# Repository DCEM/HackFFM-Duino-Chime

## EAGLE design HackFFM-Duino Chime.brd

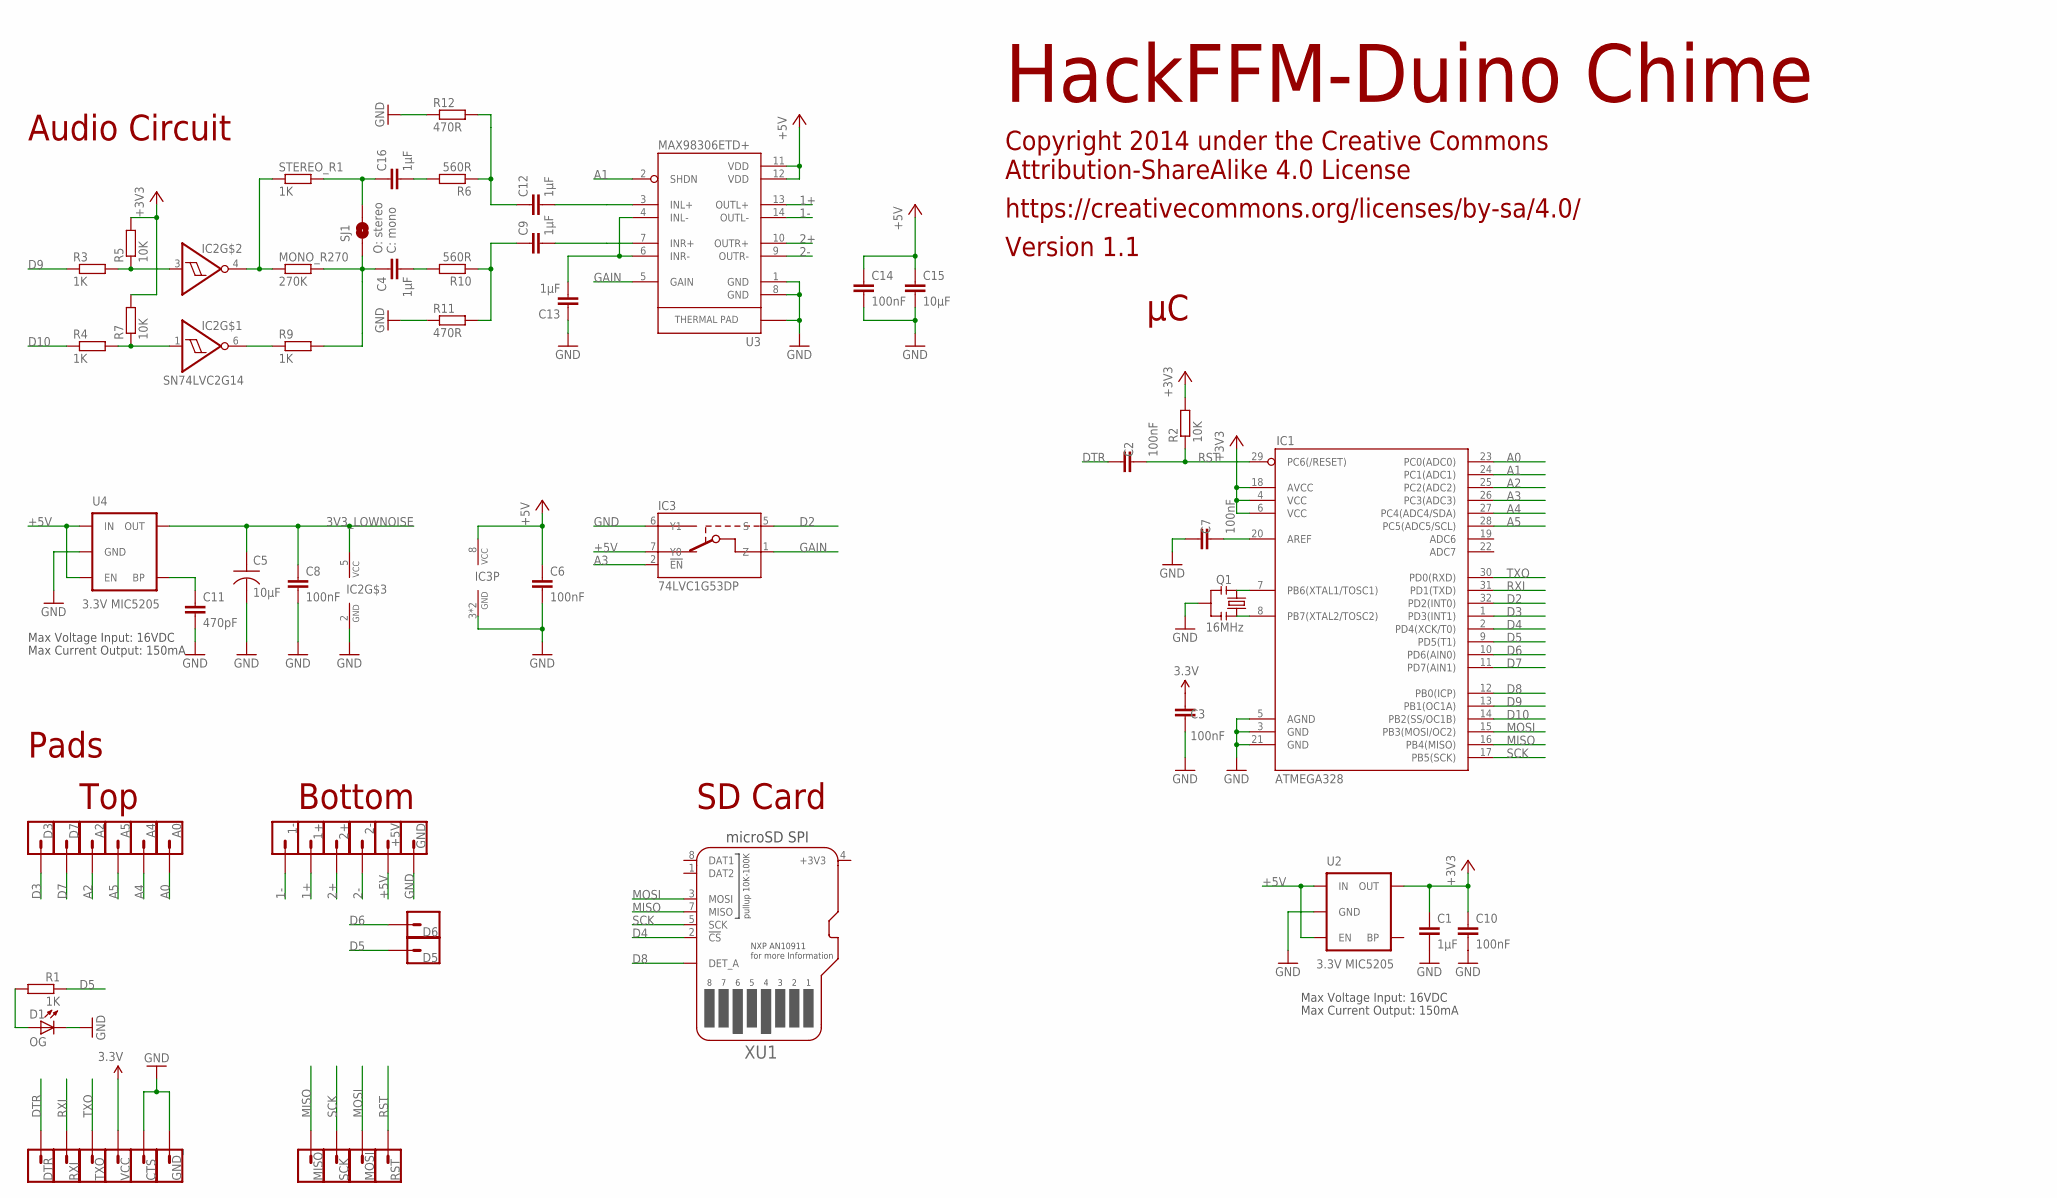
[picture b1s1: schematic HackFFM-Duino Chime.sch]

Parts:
1+, 1-, 2+, 2-: M01M01_SMD_EDGE_SHORT; M01_SMD_EDGE_SHORT
+5V: M01M01_SMD_EDGE_SHORT; M01_SMD_EDGE_SHORT
A0, A2, A4, A5: M01M01_SMD_EDGE_SHORT; M01_SMD_EDGE_SHORT
C1, C4, C9, C12, C13, C16: 1µF; C0402
C2, C3, C6, C7, C8, C10, C14: 100nF; C0402
C5: 10µF; TAN-A
C11: 470pF; C0402
C15: 10µF; C0805
CTS: M01M01_SMD_EDGE_XS; M01_SMD_EDGE_XS
D1: OG; LED-0603
D3, D5, D6, D7: M01M01_SMD_EDGE_SHORT; M01_SMD_EDGE_SHORT
DTR: M01M01_SMD_EDGE_XS; M01_SMD_EDGE_XS
GND: M01M01_SMD_EDGE_SHORT; M01_SMD_EDGE_SHORT
GND_: M01M01_SMD_EDGE_XS; M01_SMD_EDGE_XS
IC1: ATMEGA328; TQFP32-08
IC2: SN74LVC2G14; DCK_(R-PDSO-G6)
IC3: 74LVC1G53DP; SOT-505-2
MISO: M01M01_SMD_EDGE_XS; M01_SMD_EDGE_XS
MONO_R270: 270K; R0805_NOCREAM
MOSI: M01M01_SMD_EDGE_XS; M01_SMD_EDGE_XS
Q1: 16MHz; RESONATOR-SMD
R1, R3, R4, R9: 1K; R0402
R2, R5, R7: 10K; R0402
R6, R10: 560R; R0402
R11, R12: 470R; R0402
RST: M01M01_SMD_EDGE_XS; M01_SMD_EDGE_XS
RXI: M01M01_SMD_EDGE_XS; M01_SMD_EDGE_XS
SCK: M01M01_SMD_EDGE_XS; M01_SMD_EDGE_XS
SJ1: SOLDERJUMPERNO; SJ_2S-NO
STEREO_R1: 1K; R0805_NOCREAM
TXO: M01M01_SMD_EDGE_XS; M01_SMD_EDGE_XS
U2, U4: 3.3V MIC5205; SOT23-5
U3: MAX98306ETD+; 14-TDFN
VCC: M01M01_SMD_EDGE_XS; M01_SMD_EDGE_XS
XU1: MICROSD_DETMOLEX104031; MICROSD_MOLEX_104031

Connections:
1+: 1+.P$1, U3.13 (OUTL+)
1-: 1-.P$1, U3.14 (OUTL-)
2+: 2+.P$1, U3.10 (OUTR+)
2-: 2-.P$1, U3.9 (OUTR-)
3V3_LOWNOISE: C5.1, C8.1, IC2.5 (VCC), U4.5 (OUT)
+3V3: C1.1, C3.2, C10.1, IC1.4 (VCC), IC1.6 (VCC), IC1.18 (AVCC), R2.2, R5.2, R7.2, U2.5 (OUT), VCC.P$1, XU1.4 (+3V3)
+5V: +5V.P$1, C6.1, C14.1, C15.1, IC3.7 (Y0), IC3.8 (VCC), U2.1 (IN), U2.3 (EN), U3.11 (VDD), U3.12 (VDD), U4.1 (IN), U4.3 (EN)
A0: A0.P$1, IC1.23 (PC0(ADC0))
A1: IC1.24 (PC1(ADC1)), U3.2 (SHDN)
A2: A2.P$1, IC1.25 (PC2(ADC2))
A3: IC1.26 (PC3(ADC3)), IC3.2 (!EN)
A4: A4.P$1, IC1.27 (PC4(ADC4/SDA))
A5: A5.P$1, IC1.28 (PC5(ADC5/SCL))
D2: IC1.32 (PD2(INT0)), IC3.5 (S)
D3: D3.P$1, IC1.1 (PD3(INT1))
D4: IC1.2 (PD4(XCK/T0)), XU1.2 (!CS)
D5: D5.P$1, IC1.9 (PD5(T1)), R1.1
D6: D6.P$1, IC1.10 (PD6(AIN0))
D7: D7.P$1, IC1.11 (PD7(AIN1))
D8: IC1.12 (PB0(ICP)), XU1.DET_A
D9: IC1.13 (PB1(OC1A)), R3.1
D10: IC1.14 (PB2(SS/OC1B)), R4.1
DTR: C2.2, DTR.P$1
GAIN: IC3.1 (Z), U3.5 (GAIN)
GND: C1.2, C3.1, C5.2, C6.2, C7.2, C8.2, C10.2, C11.2, C13.1, C14.2, C15.2, CTS.P$1, D1.C, GND.P$1, GND_.P$1, IC1.3 (GND), IC1.5 (AGND), IC1.21 (GND), IC2.2 (GND), IC3.3 (GND), IC3.4 (GND), IC3.6 (Y1), Q1.2, R11.1, R12.1, U2.2 (GND), U3.1 (GND), U3.8 (GND), U3.15 (GND), U4.2 (GND), XU1.6 (GND), XU1.DET_B (GND), XU1.G1 (GND), XU1.G2 (GND), XU1.G3 (GND), XU1.G4 (GND)
MISO: IC1.16 (PB4(MISO)), MISO.P$1, XU1.7 (MISO)
MOSI: IC1.15 (PB3(MOSI/OC2)), MOSI.P$1, XU1.3 (MOSI)
unnamed: IC1.8 (PB7(XTAL2/TOSC2)), Q1.1
unnamed: IC1.7 (PB6(XTAL1/TOSC1)), Q1.3
unnamed: D1.A, R1.2
unnamed: C16.2, R6.2
unnamed: IC2.1 (I), R4.2, R7.1
unnamed: C11.1, U4.4 (BP)
unnamed: C12.1, R6.1, R12.2
unnamed: IC2.3 (I), R3.2, R5.1
unnamed: IC2.6 (O), R9.1
unnamed: IC2.4 (O), MONO_R270.1, STEREO_R1.1
unnamed: C4.2, R10.2
unnamed: C9.1, R10.1, R11.2
unnamed: C9.2, U3.7 (INR+)
unnamed: C4.1, MONO_R270.2, R9.2, SJ1.1
unnamed: C16.1, SJ1.2, STEREO_R1.2
unnamed: C7.1, IC1.20 (AREF)
unnamed: C13.2, U3.4 (INL-), U3.6 (INR-)
unnamed: C12.2, U3.3 (INL+)
RST: C2.1, IC1.29 (PC6(/RESET)), R2.1, RST.P$1
RXI: IC1.31 (PD1(TXD)), RXI.P$1
SCK: IC1.17 (PB5(SCK)), SCK.P$1, XU1.5 (SCK)
TXO: IC1.30 (PD0(RXD)), TXO.P$1

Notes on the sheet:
Max Voltage Input: 16VDC
Max Current Output: 150mA
HackFFM-Duino Chime
Copyright 2014 under the Creative Commons Attribution-ShareAlike 4.0 License
https://creativecommons.org/licenses/by-sa/4.0/
Audio Circuit
Pads
SD Card
Top
Bottom
Version 1.1
O: stereo C: mono

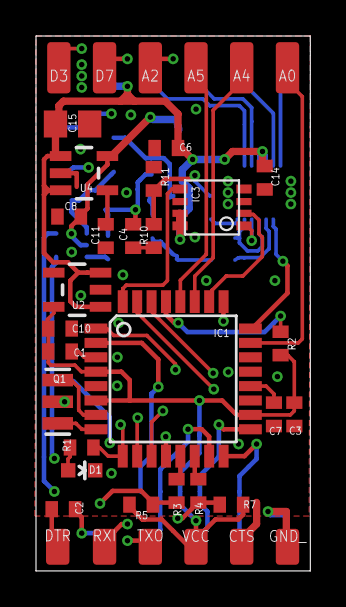
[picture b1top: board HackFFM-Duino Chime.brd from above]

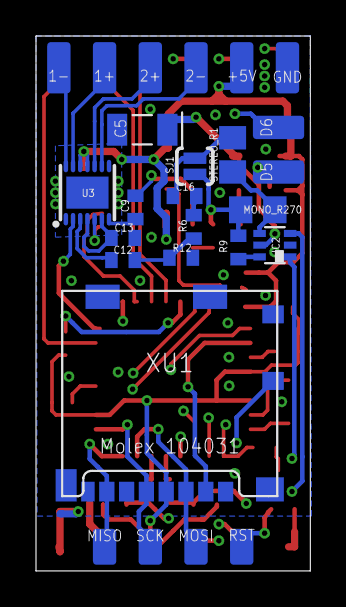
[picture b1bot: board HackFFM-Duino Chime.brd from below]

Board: 4 copper layers, 15.2 x 29.7 mm, 63 parts (26 on the bottom side), 49 nets.

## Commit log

2014-09-05 :boom::camel: Added .gitattributes & .gitignore files
2014-09-05 initial release
2015-09-26 Version 1.1 update
